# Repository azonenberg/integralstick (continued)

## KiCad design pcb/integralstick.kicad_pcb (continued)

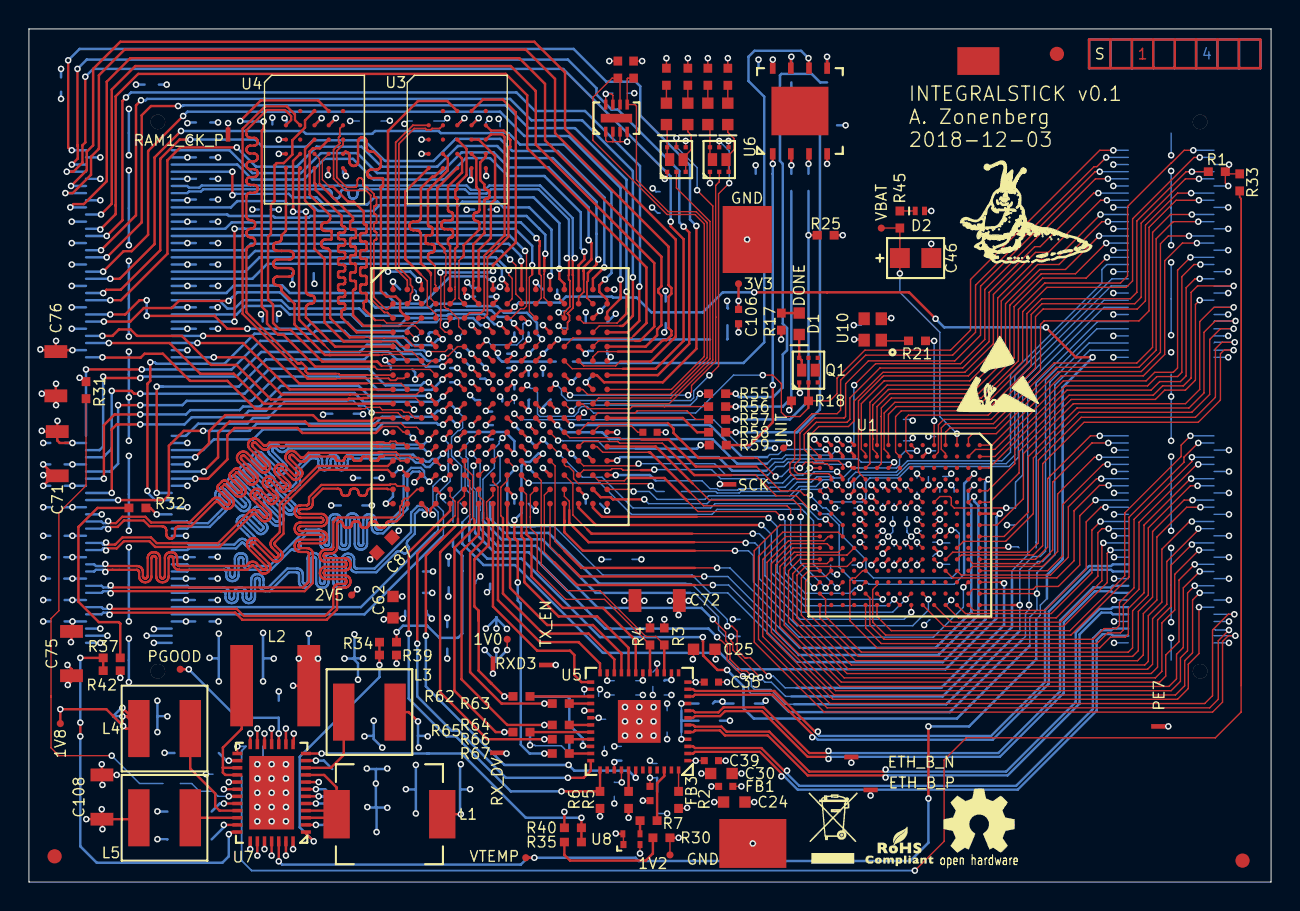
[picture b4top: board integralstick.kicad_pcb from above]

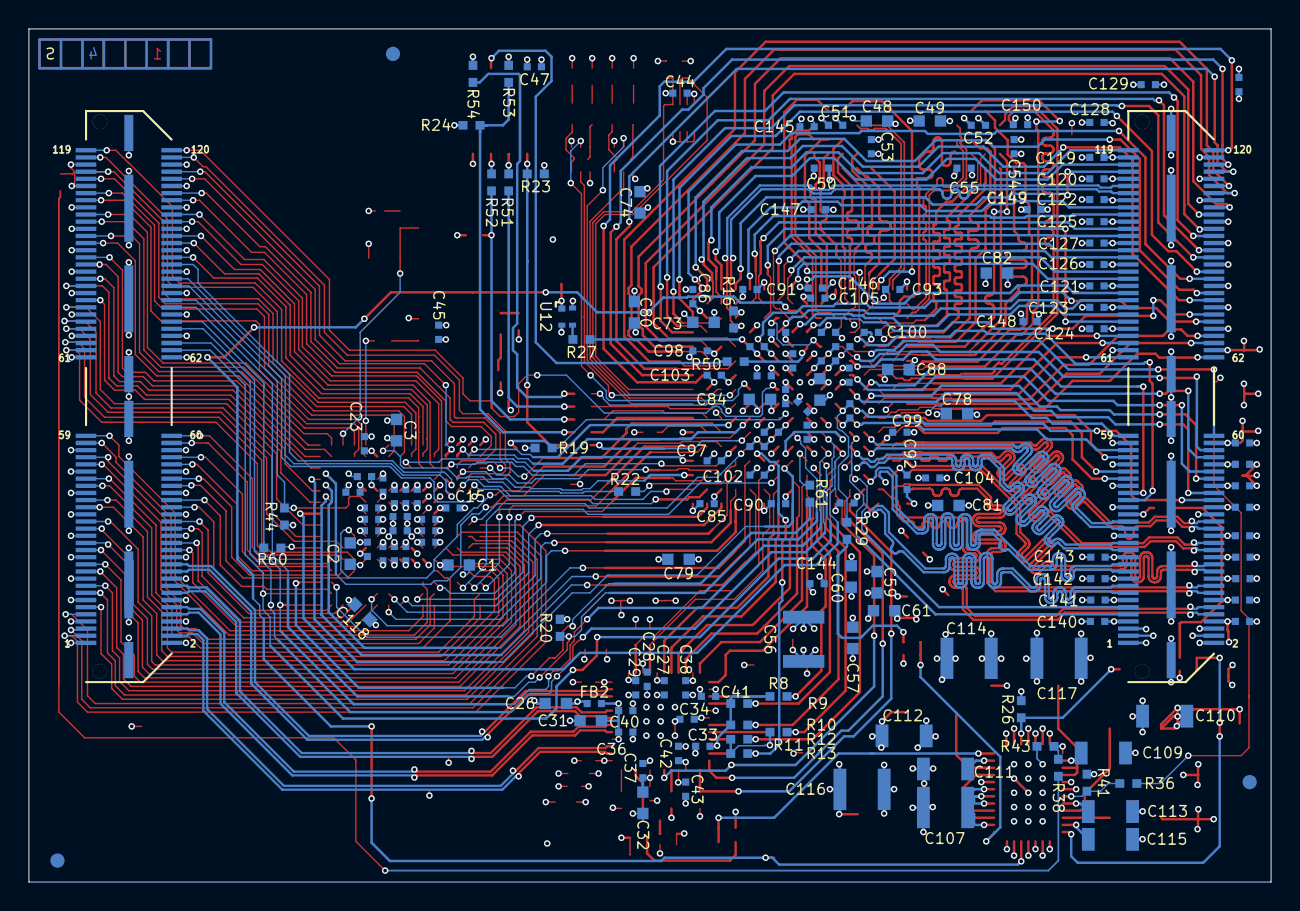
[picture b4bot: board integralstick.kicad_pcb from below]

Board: 4 copper layers, 87.0 x 59.8 mm, 272 parts (170 on the bottom side), 311 nets.

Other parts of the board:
FIDUCIAL_1MM, FIDUCIAL_1MM#2, FIDUCIAL_1MM#3, FIDUCIAL_1MM#4, FIDUCIAL_1MM#5, FIDUCIAL_1MM#6: VAL**; FIDUCIAL_1MM

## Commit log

2018-11-06 Initial schematic. Still needs PSU and review plus FPGA decoupling.
2018-11-07 Finished initial schematic. Pin assignments will likely change during routing. Ready for test point insertion and signoff review.
2018-11-07 Initial schematic for design review
2018-11-07 Changed IN_3V3_0_P/N to be on a MRCC pin so we can use it as an LVDS input clock
2018-11-07 Added pulldown to BOOT0 on MCU, brought it out to previously unused connector pin
2018-11-07 Re-rendered design review schematic with recent board changes
2018-11-08 Updated design review schematic
2018-11-08 Added capacitor for bbRAM on STM32. Removed MCU config oscillator, we now use the FPGA or internal oscillator as clock. Added SPI bus from FPGA to MCU.
2018-11-08 Added four GPIO LEDs
2018-11-09 Finished schematic signoff review. Fixed oscillator pinout bug, added some test points.
2018-11-09 Updated schematic after design review
2018-11-09 Assigned lots of footprints. Still have a few to go.
2018-11-09 Assigned inductor footprints
2018-11-09 Initial design rules
2018-11-09 Added stackup/impedance notes
2018-11-10 Finished initial footprint assignments
2018-11-11 Initial work on FPGA fanout
2018-11-12 Finished first iteration layout of RAM. Lots of pin swaps.
2018-11-12 Initial BGA fanout for 3.3V GPIO. Not complete.
2018-11-12 Now ignoring fp-info-cache
2018-11-13 Lots more routing of 3.3V GPIO bus
2018-11-13 Continued routing 3.3V GPIO bus. Everything that can be fanned out on top metal is done.
2018-11-13 Finished routing 3.3V GPIO bus
2018-11-13 Added layer-change caps by Q-strip
2018-11-13 Initial FPGA plane layout
2018-11-13 Began work on LVCMOS18 GPIOs. Swapped a lot of pins around.
2018-11-13 More efficient use of top right area above FPGA
2018-11-13 Initial routing of LVCMOS18 GPIO bus. Hooked up a few 0603 decoupling caps.
2018-11-14 Initial layout of LVDS bank
2018-11-14 Added missing 1V8 clock. Tweaked planes. Added some layer change caps.
2018-11-17 Continued FPGA layout. Fanned out most signals going to MCU but pin assignments aren't final.
2018-11-17 Fixed diffpair DRC issues
2018-11-19 Initial placement of SMPS and inductors. No caps.
2018-11-20 Continued work on layout. Added some layer crossing caps. Initial power plane placement.
2018-11-21 Initial STM32 fanout
2018-11-24 Finished initial routing
2018-11-28 Updated pin cache
2018-11-30 Added lots of test points
2018-12-03 Final PCB design being sent to fab for quotes
2018-12-03 Changed soldermask web size to something more sane
2018-12-03 Fixed C124 silkscreen over component pad
2018-12-03 Added e-test netlist to ignore, added gerbv project
2018-12-03 Updated project with correct soldermask width
2019-01-11 Updated integralstick schematic to fix library paths. No content changes.
2019-01-11 Initial version of mintest-left
2019-01-11 Initial version of mintest-right board
2019-01-11 Added fp cache
2019-08-14 Initial test firmware
2019-08-14 Initial blinky toggle working
2019-11-04 Updated caches and hello test
2019-11-04 Updated tests
2019-11-04 Initial version of host-full board
2019-11-05 Finished initial schematic review
2019-11-08 Initial layout on host-full. Rough floorplan is finalized, all MCU PMODs routed.
2019-11-10 Continued host-full layout. Almost all PHY RGMII routing done
2019-11-11 Finished initial routing, still need to do planes and design review
2019-11-11 Initial plane layout. Still need more work on power layers.
2019-11-11 Finished tweaking zone fills. Ready for signoff review.
2019-11-11 Various fixes during layout review, added some silkscreen labels and a layer-change cap
2019-11-11 Added fab notes and gerbview project
2019-11-18 Updated ignore for gerber zip
2019-11-28 Removed stray noconnect marker
